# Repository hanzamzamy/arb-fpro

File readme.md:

# ARb Project
## Introduction
ARb is a robotic arm with 4 degrees of freedom. It is designed to be used in a variety of applications, including pick and place, etc. The arm is controlled by a host computer, which communicates with an STM32 to control the servos using UART via USB. The arm is also equipped with a sensor and a gripper, which can be used to pick up and manipulate objects. The arm is designed to be easy to use. The arm also designed to be affordable, with a total cost of less than Rp500.000,00. _Although we spent more because of trial and error, and we also bought some parts in a higher price than the market price._
## Features
- 4 degrees of freedom
- 1 gripper with integrated sensor
- Automatic find and pick up object
- Easy to use
- Fully programmable
## Components
- 3x MG996R Servo
- 2x MG90S Servo
- 1x VL53L0X Sensor
- 1x STM32F401CCU6
- 1x LM2596 DC-DC Step Down
- Custom PCB and Acrylic parts
## Tech Stack
- C -> STM32
    - HAL -> Hardware Abstraction Layer
    - VL53L0X -> Sensor
    - USB CDC -> Communication
- Python -> Host Computer
  - PySerial -> Communication
  - IKPy -> Inverse Kinematics
- Solidworks -> Design
- KiCad -> PCB Design
## Expenditure
[Rincian_Anggaran.pdf](https://github.com/hanzamzamy/arb-fpro/blob/master/Rincian_Anggaran.pdf)
## Documentation
[Video Demo.mp4](https://github.com/hanzamzamy/arb-fpro/blob/master/Dokumentasi/Video%20Demo.mp4)
[Robot.jpg](https://github.com/hanzamzamy/arb-fpro/blob/master/Dokumentasi/Barang%20e.jpg)
[Photo1.jpg](https://github.com/hanzamzamy/arb-fpro/blob/master/Dokumentasi/1.jpg)
[Photo2.jpg](https://github.com/hanzamzamy/arb-fpro/blob/master/Dokumentasi/1.jpg)
## Team
- Mechanical - [Silvia Nur Aziza]()
- Electrical - [Rayhan Rizqi Zamzamy](https://github.com/hanzamzamy)
- Programming - [Nabiel Nizar Anwari](https://github.com/bielnzar)

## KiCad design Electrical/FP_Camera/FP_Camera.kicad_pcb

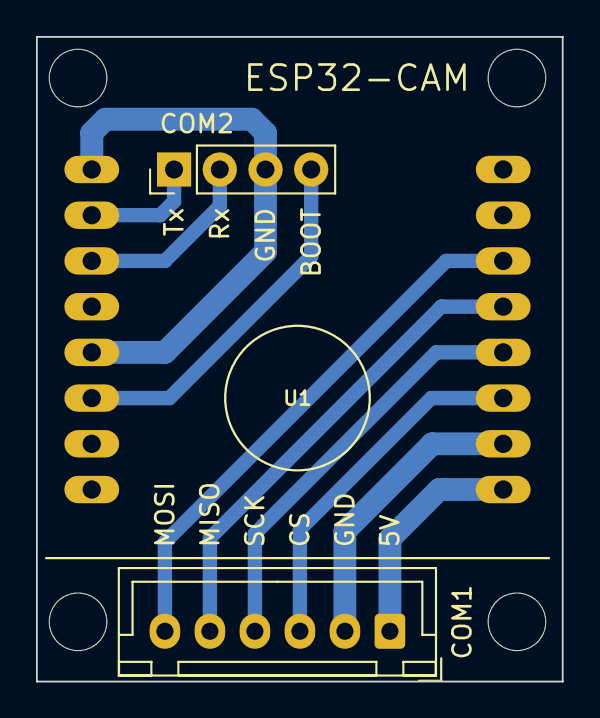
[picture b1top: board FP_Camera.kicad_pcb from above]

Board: 2 copper layers, 29.2 x 35.8 mm, 3 parts (0 on the bottom side), 9 nets.

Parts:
COM1: STM32; JST_XH_B6B-XH-A_1x06_P2.50mm_Vertical
COM2: USB-TTL; PinHeader_1x04_P2.54mm_Vertical
U1: ESP32-CAM

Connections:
+5V: COM1.1, U1.P$9 (5V)
BOOT: COM2.4, U1.P$6 (GPIO0)
CSEL: COM1.3, U1.P$11 (GPIO12)
GND: COM1.2, COM2.3, U1.P$1 (GND@1), U1.P$5 (GND@2), U1.P$10 (GND@3)
MISO: COM1.5, U1.P$13 (GPIO15)
MOSI: COM1.6, U1.P$14 (GPIO14)
RX: COM2.2, U1.P$3 (GPIO3)
SCLK: COM1.4, U1.P$12 (GPIO13)
TX: COM2.1, U1.P$2 (GPIO1)

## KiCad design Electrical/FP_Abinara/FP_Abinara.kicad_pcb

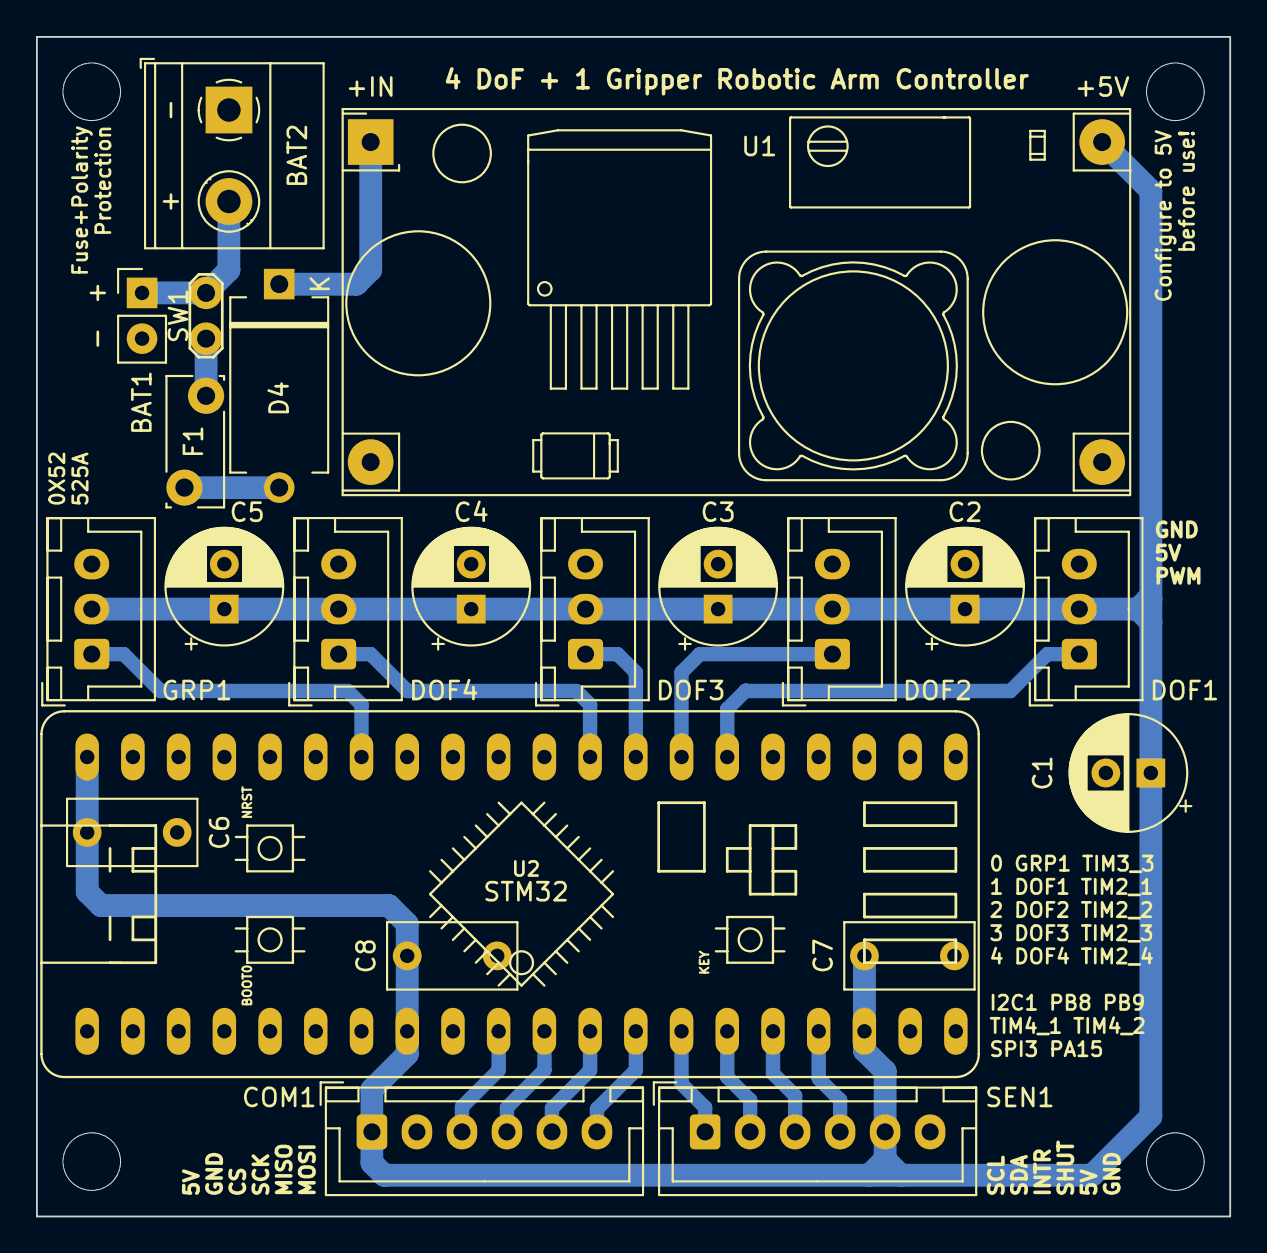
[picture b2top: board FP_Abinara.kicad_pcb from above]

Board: 2 copper layers, 66.3 x 65.5 mm, 22 parts (0 on the bottom side), 19 nets.

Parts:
BAT1: JST-RE; PinHeader_1x02_P2.54mm_Vertical
BAT2: Terminal Block; TerminalBlock_Phoenix_MKDS-1,5-2-5.08_1x02_P5.08mm_Horizont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
C1, C2, C3, C4, C5: 220u; CP_Radial_D6.3mm_P2.50mm
C6, C7, C8: 220n; C_Rect_L7.0mm_W3.5mm_P5.00mm
COM1: ESP32-CAM; JST_XH_B6B-XH-A_1x06_P2.50mm_Vertical
D4: 1N5822; D_DO-201AD_P12.70mm_Horizontal
DOF1, DOF2: MG995; JST_XH_B3B-XH-A_1x03_P2.50mm_Vertical
DOF3, DOF4: MG90; JST_XH_B3B-XH-A_1x03_P2.50mm_Vertical
F1: 6A; Fuse_Bourns_MF-RG300
GRP1: MG90; JST_XH_B3B-XH-A_1x03_P2.50mm_Vertical
SEN1: VL53L0X; JST_XH_B6B-XH-A_1x06_P2.50mm_Vertical
SW1: SW_SPST; TestPoint_2Pads_Pitch2.54mm_Drill0.8mm
U1: StepDown_LM2596; YAAJ_DCDC_StepDown_LM2596
U2: BLACK_PILL

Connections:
+5V: C1.1, C2.1, C3.1, C4.1, C5.1, C6.1, C7.1, C8.1, COM1.1, DOF1.2, DOF2.2, DOF3.2, DOF4.2, GRP1.2, SEN1.5, U1.4 (Vout), U2.5V, U2.5V1, U2.PA11
+12V: BAT1.1, BAT2.2, SW1.1 (A)
CSEL: COM1.3, U2.PA15
GND: BAT1.2, BAT2.1, C1.2, C2.2, C3.2, C4.2, C5.2, C6.2, C7.2, C8.2, COM1.2, DOF1.3, DOF2.3, DOF3.3, DOF4.3, GRP1.3, SEN1.6, U1.2 (GND), U1.3 (GND), U2.GND, U2.GND1, U2.PA12
INTR: SEN1.3, U2.PB8
MISO: COM1.5, U2.PB4
MOSI: COM1.6, U2.PB5
unnamed: D4.2 (A), F1.2
unnamed: D4.1 (K), U1.1 (Vin)
unnamed: F1.1, SW1.2 (B)
PWM1: DOF1.1, U2.PA0
PWM2: DOF2.1, U2.PA1
PWM3: DOF3.1, U2.PA2
PWM4: DOF4.1, U2.PA3
PWM5: GRP1.1, U2.PB0
SCL: SEN1.1, U2.PB6
SCLK: COM1.4, U2.PB3
SDA: SEN1.2, U2.PB7
SHUT: SEN1.4, U2.PB9

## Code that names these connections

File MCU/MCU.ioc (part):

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Mcu.Name=STM32F401C(B-C)Ux
Mcu.Package=UFQFPN48
Mcu.UserName=STM32F401CCUx
PA0-WKUP.GPIOParameters=GPIO_Speed,GPIO_Label
PA0-WKUP.GPIO_Label=DOF_1
PA0-WKUP.GPIO_Speed=GPIO_SPEED_FREQ_HIGH
PA0-WKUP.Signal=S_TIM2_CH1_ETR
PA1.GPIOParameters=GPIO_Speed,GPIO_Label
PA1.GPIO_Label=DOF_2
PA1.GPIO_Speed=GPIO_SPEED_FREQ_HIGH
PA1.Signal=S_TIM2_CH2
PA11.Mode=Device_Only
PA11.Signal=USB_OTG_FS_DM
PA12.Mode=Device_Only
PA12.Signal=USB_OTG_FS_DP
PA2.GPIOParameters=GPIO_Speed,GPIO_Label
PA2.GPIO_Label=DOF_3
PA2.GPIO_Speed=GPIO_SPEED_FREQ_HIGH
PA2.Signal=S_TIM2_CH3
PA3.GPIOParameters=GPIO_Speed,GPIO_Label
PA3.GPIO_Label=DOF_4
PA3.GPIO_Speed=GPIO_SPEED_FREQ_HIGH
PA3.Signal=S_TIM2_CH4
PB0.GPIOParameters=GPIO_Speed,GPIO_Label
PB0.GPIO_Label=GRP_1
PB0.GPIO_Speed=GPIO_SPEED_FREQ_HIGH
PB0.Signal=S_TIM3_CH3
PB6.GPIOParameters=GPIO_Speed,GPIO_Label
PB6.GPIO_Label=SCL
PB6.GPIO_Speed=GPIO_SPEED_FREQ_VERY_HIGH
PB6.Mode=I2C
PB6.Signal=I2C1_SCL
PB7.GPIOParameters=GPIO_Speed,GPIO_Label
PB7.GPIO_Label=SDA
PB7.GPIO_Speed=GPIO_SPEED_FREQ_VERY_HIGH
PB7.Mode=I2C
PB7.Signal=I2C1_SDA
PB8.GPIOParameters=GPIO_Label,GPIO_ModeDefaultEXTI
PB8.GPIO_Label=VL_INT
PB8.GPIO_ModeDefaultEXTI=GPIO_MODE_IT_RISING
PB8.Signal=GPXTI8
PB9.GPIOParameters=PinState,GPIO_Label
PB9.GPIO_Label=VL_SHT
PB9.PinState=GPIO_PIN_SET
PB9.Signal=GPIO_Output
PC13-ANTI_TAMP.GPIOParameters=GPIO_Label
PC13-ANTI_TAMP.GPIO_Label=LED
PC13-ANTI_TAMP.Signal=GPIO_Output
PH0\ -\ OSC_IN.Mode=HSE-External-Oscillator
PH0\ -\ OSC_IN.Signal=RCC_OSC_IN
PH1\ -\ OSC_OUT.Mode=HSE-External-Oscillator
PH1\ -\ OSC_OUT.Signal=RCC_OSC_OUT
RCC.HSE_VALUE=25000000
RCC.SYSCLKFreq_VALUE=84000000
RCC.SYSCLKSource=RCC_SYSCLKSOURCE_PLLCLK
board=custom

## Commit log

2024-02-21 something
2024-02-21 add full code
2024-02-21 Create LICENSE
2024-02-21 minor change on experimental function
2024-02-22 change action()
2024-02-22 change action() again [2]
2024-02-22 halo halo bandung
2024-02-22 cendol balado
2024-02-22 keripik kukus
2024-02-22 pudding crispy
2024-02-22 rendang bakar
2024-02-22 lemper rebus
2024-02-22 tumis bakwan
2024-02-22 Rename ANGGARAN.pdf to Rincian_Anggaran.pdf
2024-02-22 Rename Succes.mp4 to Video Demo.mp4
2024-02-22 pecak jahe
2024-02-22 mendoan presto
2024-02-22 sup ketupat
2024-02-22 semur sambel
